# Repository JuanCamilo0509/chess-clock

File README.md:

# Chess Clock
It's a simple chess clock ready to play, although it hasn't been tested yet. But the only detail I'm not sure about is the USB-C connection in the schematic and maybe some fool error with KiCad that I haven't noticed. However the C code and the circuit in simulide works.
If you want to colaborate on fixing something in the code, in the schematic or if you just want to see the circuit working with the code, all that stuff is in the folders of the repository.

> I'm trying to improve the pcb, sorry for those who saw the first commit xd.
## How to use:
There are two buttons in the bottom of the PCB. One of them is for add one to both counters. And the other one is to reset the time to 0.
Just connect, reset, set up the time and play.
## Parts:
- (1) Atmega328-AU.
- (2) Four digits 7 segement display.
- (2) Mx switches.
- (2) Hotswap sockets.
- (2) Push buttons.
- (3) 1k resistors.
- (2) 5.11K resistor.
- (1) 1M resistor.
- (1) USB-C port 6 pins.
- (3) Spacers
- (3) Screws

## Sofware I used
- Kicad.
- Fusion 360.
- Simulide.
- Microchip Studio.

Feel free to collaborate with me; I'll be very happy to talk with you. :DD

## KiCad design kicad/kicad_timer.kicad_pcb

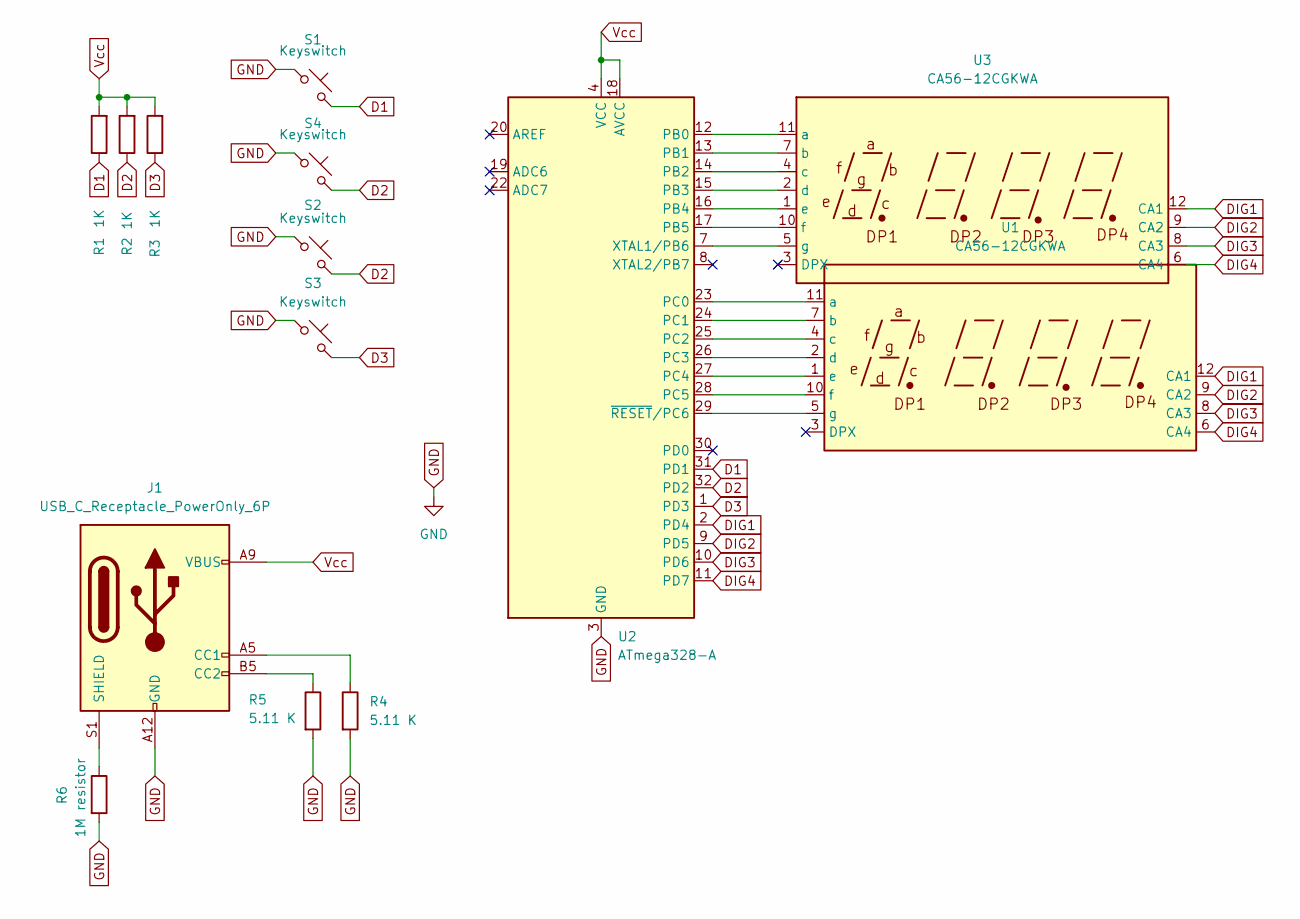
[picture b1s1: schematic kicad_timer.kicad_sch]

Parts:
J1: USB_C_Receptacle_PowerOnly_6P; USB_C_Receptacle_GCT_USB4125-xx-x_6P_TopMnt_Horizontal
R1, R2, R3: 1K; R_0201_0603Metric
R4, R5: 5.11 K; R_0201_0603Metric
R6: 1M resistor; R_0201_0603Metric
S1, S4: Keyswitch; SW_Push_1P1T-SH_NO_CK_KMR2xxG
S2, S3: Keyswitch; keyswitch_cherrymx_hotswap_1u
U1, U3: CA56-12CGKWA
U2: ATmega328-A; TQFP-32_7x7mm_P0.8mm

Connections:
D1: R1.1, S1.2, U2.31 (PD1)
D2: R2.1, S2.2, S4.2, U2.32 (PD2)
D3: R3.1, S3.2, U2.1 (PD3)
DIG1: U1.12 (CA1), U2.2 (PD4), U3.12 (CA1)
DIG2: U1.9 (CA2), U2.9 (PD5), U3.9 (CA2)
DIG3: U1.8 (CA3), U2.10 (PD6), U3.8 (CA3)
DIG4: U1.6 (CA4), U2.11 (PD7), U3.6 (CA4)
GND: J1.A12 (GND), J1.B12 (GND), R4.2, R5.2, R6.2, S1.1, S2.1, S3.1, S4.1, U2.3 (GND), U2.5 (GND), U2.21 (GND)
unnamed: J1.A5 (CC1), R4.1
unnamed: J1.B5 (CC2), R5.1
unnamed: J1.S1 (SHIELD), R6.1
unnamed: U1.11 (a), U2.23 (PC0)
unnamed: U1.7 (b), U2.24 (PC1)
unnamed: U1.4 (c), U2.25 (PC2)
unnamed: U1.2 (d), U2.26 (PC3)
unnamed: U1.1 (e), U2.27 (PC4)
unnamed: U1.10 (f), U2.28 (PC5)
unnamed: U1.5 (g), U2.29 (~RESET/PC6)
unnamed: U2.12 (PB0), U3.11 (a)
unnamed: U2.13 (PB1), U3.7 (b)
unnamed: U2.14 (PB2), U3.4 (c)
unnamed: U2.15 (PB3), U3.2 (d)
unnamed: U2.16 (PB4), U3.1 (e)
unnamed: U2.17 (PB5), U3.10 (f)
unnamed: U2.7 (XTAL1/PB6), U3.5 (g)
Vcc: J1.A9 (VBUS), J1.B9 (VBUS), R1.2, R2.2, R3.2, U2.4 (VCC), U2.6 (VCC), U2.18 (AVCC)

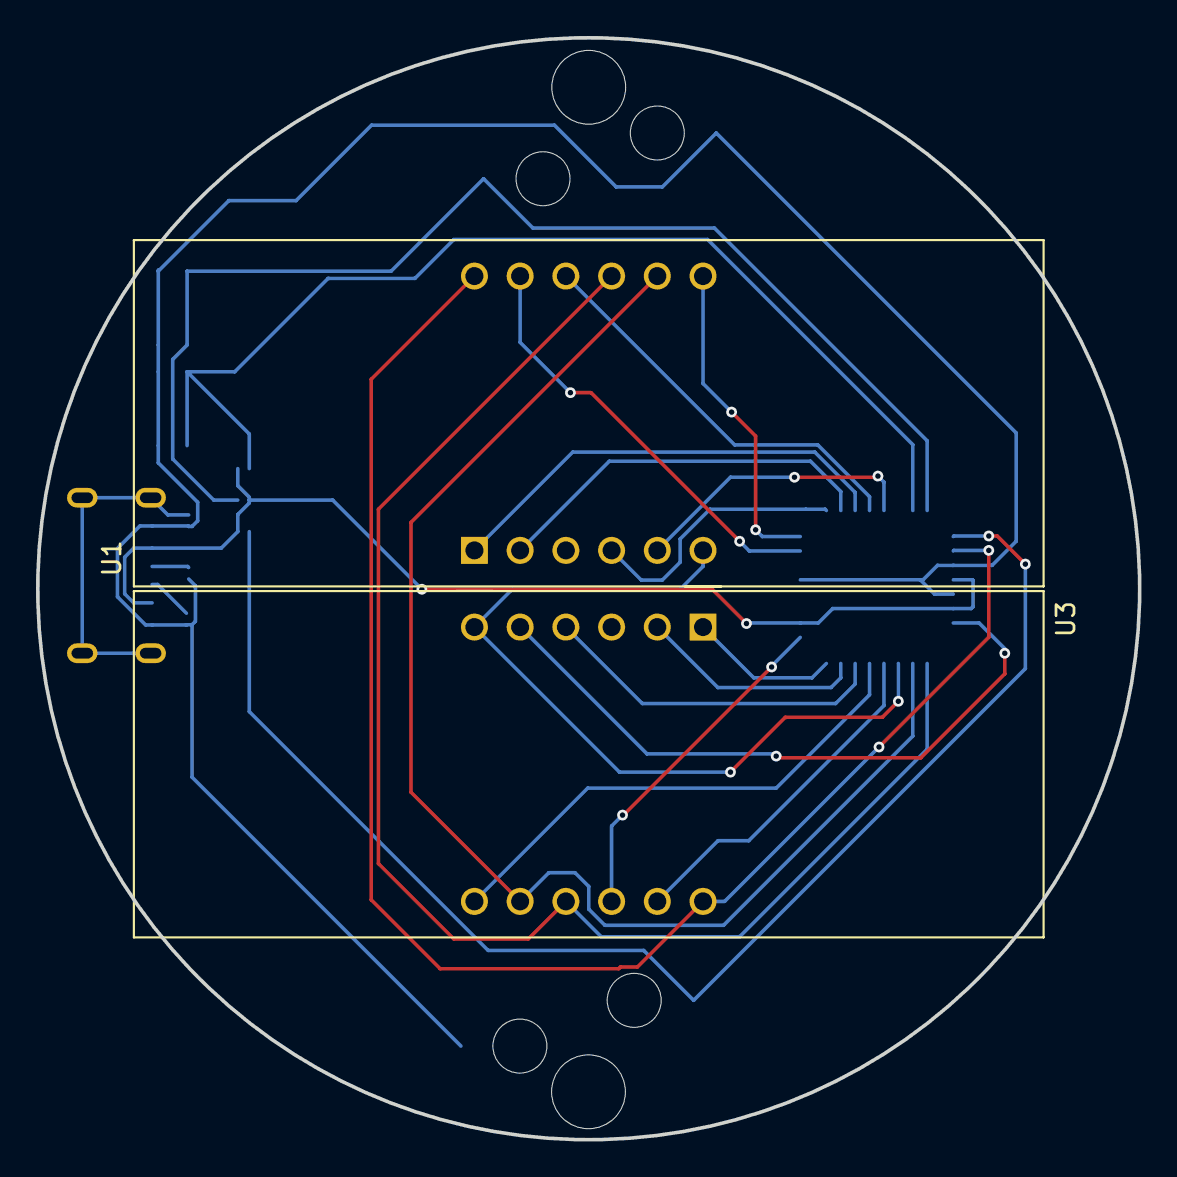
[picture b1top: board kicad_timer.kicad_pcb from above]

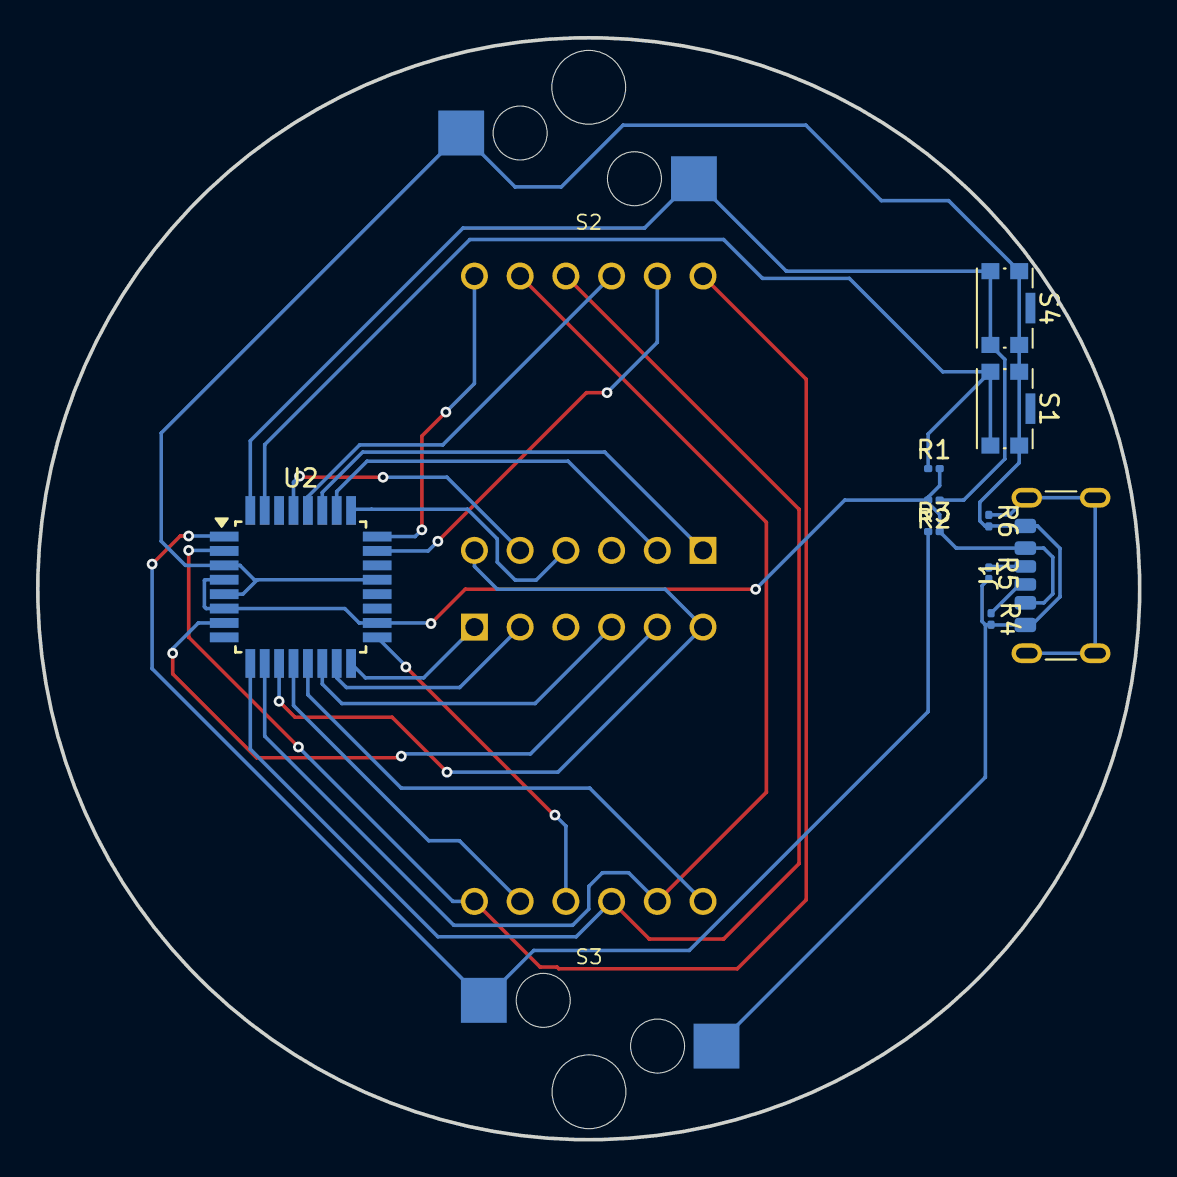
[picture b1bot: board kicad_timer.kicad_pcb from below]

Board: 2 copper layers, 61.2 x 61.2 mm, 14 parts (12 on the bottom side), 26 nets.

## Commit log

2024-07-24 Improving the pcb
